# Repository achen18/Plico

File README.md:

# Plico
Fully custom split mechanical keyboard. Runs on ZMK software, controlling key functions and responsive lighting. Future iterations intend to use ultra low-profile switches and a case redesign to allow the two sides to fold together for portability. Firmware updates plan to incorporate layers and macros once the author thinks of what to use so many keys for. 

## PCB
Designed in Kicad

Schematic

PCB

## Case  
3d printed case desinged using Fusion 360. Multiple parts designed for printing with minimal supports. Designed such that no mounting holes needed in pcb. 

## Firmware  
Macropad runs on ZMK software.  
- Split keyboard Bluetooth connection
- 44 keys, full keyboard functionality
- Reactive key leds with fade out effects

To-Do
- Multiple layers for different day-to-day needs. Custom key to easily cycle between layers. Indicate current layer with rgb change. 

## Bill of Materials  
- 2 x XIAO-nRF52840-SMD
- 44 x 1N5819 SMD Diodes
- 44 x MX-Style switches
- 44 x Blank DSA keycaps
- 44 x SK6812-E Reverse Mount LEDs
- 2 x Resistors (1 806k, 1 2M)
- 10 x M3x10 Screws
- 10 x M3x5mx4mm heatset inserts
- 1 x Case (6 3D printed parts - 3 left/right)

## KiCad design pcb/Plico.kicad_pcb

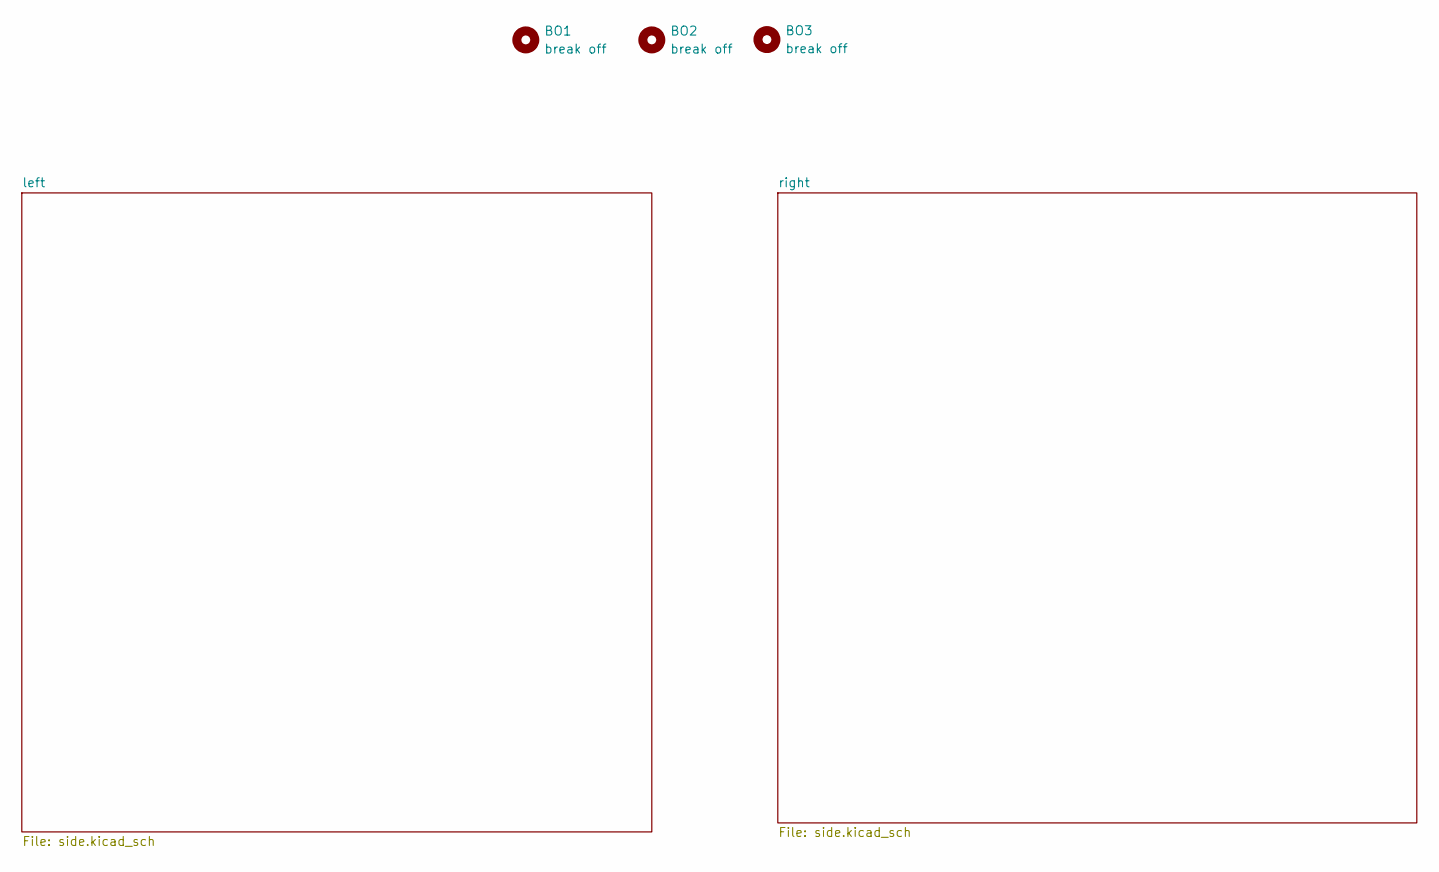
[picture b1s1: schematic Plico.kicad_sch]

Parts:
BO1, BO2, BO3: break off; mouse-bite-5mm-slot-edgeCuts

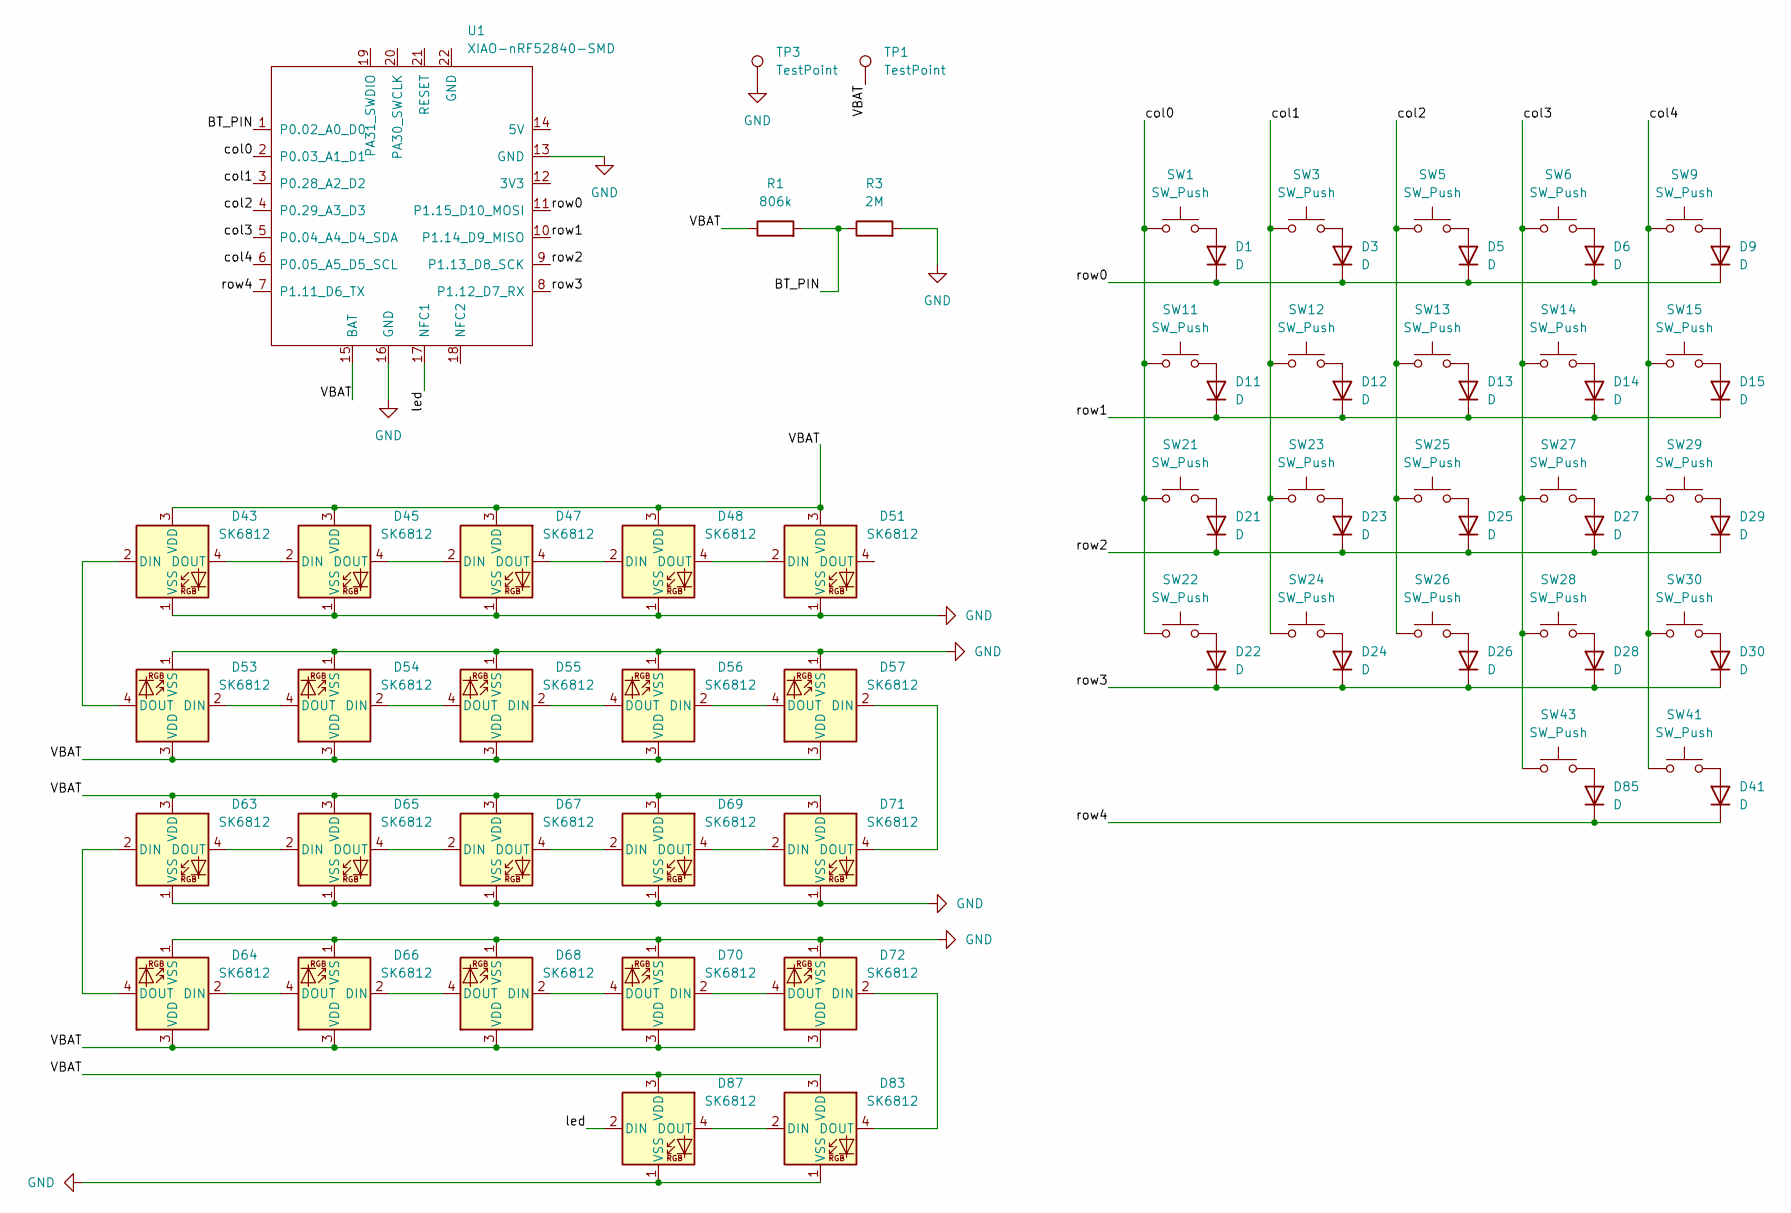
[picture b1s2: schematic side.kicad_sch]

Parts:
D1, D3, D5, D6, D9, D11, D12, D13, D14, D15, D21, D22, D23, D24, D25, D26, D27, D28, D29, D30, D41, D85: D; D_SOD-123
D43, D45, D47, D48, D51, D53, D54, D55, D56, D57, D63, D64, D65, D66, D67, D68, D69, D70, D71, D72, D83, D87: SK6812; Untitled
R1: 806k; R_0805_2012Metric
R3: 2M; R_0805_2012Metric
SW1, SW3, SW5, SW6, SW9, SW11, SW12, SW13, SW14, SW15, SW21, SW22, SW23, SW24, SW25, SW26, SW27, SW28, SW29, SW30, SW41, SW43: SW_Push; SW_MX_HS_CPG151101S11_1u
TP1, TP3: TestPoint; TestPoint_Pad_D2.0mm
U1: XIAO-nRF52840-SMD; modified-XIAO-nRF52840-SMD

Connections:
/left/BT_PIN: R1.2, R3.1, U1.1 (P0.02_A0_D0)
/left/VBAT: D43.3 (VDD), D45.3 (VDD), D47.3 (VDD), D48.3 (VDD), D51.3 (VDD), D53.3 (VDD), D54.3 (VDD), D55.3 (VDD), D56.3 (VDD), D57.3 (VDD), D63.3 (VDD), D64.3 (VDD), D65.3 (VDD), D66.3 (VDD), D67.3 (VDD), D68.3 (VDD), D69.3 (VDD), D70.3 (VDD), D71.3 (VDD), D72.3 (VDD), D83.3 (VDD), D87.3 (VDD), R1.1, TP1.1, U1.15 (BAT)
/left/col0: SW1.1, SW11.1, SW21.1, SW22.1, U1.2 (P0.03_A1_D1)
/left/col1: SW3.1, SW12.1, SW23.1, SW24.1, U1.3 (P0.28_A2_D2)
/left/col2: SW5.1, SW13.1, SW25.1, SW26.1, U1.4 (P0.29_A3_D3)
/left/col3: SW6.1, SW14.1, SW27.1, SW28.1, SW43.1, U1.5 (P0.04_A4_D4_SDA)
/left/col4: SW9.1, SW15.1, SW29.1, SW30.1, SW41.1, U1.6 (P0.05_A5_D5_SCL)
/left/led: D87.2 (DIN), U1.17 (NFC1)
/left/row0: D1.1 (K), D3.1 (K), D5.1 (K), D6.1 (K), D9.1 (K), U1.11 (P1.15_D10_MOSI)
/left/row1: D11.1 (K), D12.1 (K), D13.1 (K), D14.1 (K), D15.1 (K), U1.10 (P1.14_D9_MISO)
/left/row2: D21.1 (K), D23.1 (K), D25.1 (K), D27.1 (K), D29.1 (K), U1.9 (P1.13_D8_SCK)
/left/row3: D22.1 (K), D24.1 (K), D26.1 (K), D28.1 (K), D30.1 (K), U1.8 (P1.12_D7_RX)
/left/row4: D41.1 (K), D85.1 (K), U1.7 (P1.11_D6_TX)
GND: D43.1 (VSS), D45.1 (VSS), D47.1 (VSS), D48.1 (VSS), D51.1 (VSS), D53.1 (VSS), D54.1 (VSS), D55.1 (VSS), D56.1 (VSS), D57.1 (VSS), D63.1 (VSS), D64.1 (VSS), D65.1 (VSS), D66.1 (VSS), D67.1 (VSS), D68.1 (VSS), D69.1 (VSS), D70.1 (VSS), D71.1 (VSS), D72.1 (VSS), D83.1 (VSS), D87.1 (VSS), R3.2, TP3.1, U1.13 (GND), U1.16 (GND); also elsewhere on the board
unnamed: D1.2 (A), SW1.2
unnamed: D3.2 (A), SW3.2
unnamed: D5.2 (A), SW5.2
unnamed: D6.2 (A), SW6.2
unnamed: D9.2 (A), SW9.2
unnamed: D11.2 (A), SW11.2
unnamed: D12.2 (A), SW12.2
unnamed: D13.2 (A), SW13.2
unnamed: D14.2 (A), SW14.2
unnamed: D15.2 (A), SW15.2
unnamed: D21.2 (A), SW21.2
unnamed: D22.2 (A), SW22.2
unnamed: D23.2 (A), SW23.2
unnamed: D24.2 (A), SW24.2
unnamed: D25.2 (A), SW25.2
unnamed: D26.2 (A), SW26.2
unnamed: D27.2 (A), SW27.2
unnamed: D28.2 (A), SW28.2
unnamed: D29.2 (A), SW29.2
unnamed: D30.2 (A), SW30.2
unnamed: D41.2 (A), SW41.2
unnamed: D43.2 (DIN), D53.4 (DOUT)
unnamed: D43.4 (DOUT), D45.2 (DIN)
unnamed: D45.4 (DOUT), D47.2 (DIN)
unnamed: D47.4 (DOUT), D48.2 (DIN)
unnamed: D48.4 (DOUT), D51.2 (DIN)
unnamed: D53.2 (DIN), D54.4 (DOUT)
unnamed: D54.2 (DIN), D55.4 (DOUT)
unnamed: D55.2 (DIN), D56.4 (DOUT)
unnamed: D56.2 (DIN), D57.4 (DOUT)
unnamed: D57.2 (DIN), D71.4 (DOUT)
unnamed: D63.2 (DIN), D64.4 (DOUT)
unnamed: D63.4 (DOUT), D65.2 (DIN)
unnamed: D64.2 (DIN), D66.4 (DOUT)
unnamed: D65.4 (DOUT), D67.2 (DIN)
unnamed: D66.2 (DIN), D68.4 (DOUT)
unnamed: D67.4 (DOUT), D69.2 (DIN)
unnamed: D68.2 (DIN), D70.4 (DOUT)
unnamed: D69.4 (DOUT), D71.2 (DIN)
unnamed: D70.2 (DIN), D72.4 (DOUT)
unnamed: D72.2 (DIN), D83.4 (DOUT)
unnamed: D83.2 (DIN), D87.4 (DOUT)
unnamed: D85.2 (A), SW43.2

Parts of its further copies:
D2, D4, D7, D8, D10, D16, D17, D18, D19, D20, D31, D32, D33, D34, D35, D36, D37, D38, D39, D40, D42, D86: D; D_SOD-123
D44, D46, D49, D50, D52, D58, D59, D60, D61, D62, D73, D74, D75, D76, D77, D78, D79, D80, D81, D82, D84, D88: SK6812; Untitled
R2: 806k; R_0805_2012Metric
R4: 2M; R_0805_2012Metric
SW2, SW4, SW7, SW8, SW10, SW16, SW17, SW18, SW19, SW20, SW31, SW32, SW33, SW34, SW35, SW36, SW37, SW38, SW39, SW40, SW42, SW44: SW_Push; SW_MX_HS_CPG151101S11_1u
TP2, TP4: TestPoint; TestPoint_Pad_D2.0mm
U2: XIAO-nRF52840-SMD; modified-XIAO-nRF52840-SMD

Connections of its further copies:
/right/BT_PIN: R2.2, R4.1, U2.1 (P0.02_A0_D0)
/right/VBAT: D44.3 (VDD), D46.3 (VDD), D49.3 (VDD), D50.3 (VDD), D52.3 (VDD), D58.3 (VDD), D59.3 (VDD), D60.3 (VDD), D61.3 (VDD), D62.3 (VDD), D73.3 (VDD), D74.3 (VDD), D75.3 (VDD), D76.3 (VDD), D77.3 (VDD), D78.3 (VDD), D79.3 (VDD), D80.3 (VDD), D81.3 (VDD), D82.3 (VDD), D84.3 (VDD), D88.3 (VDD), R2.1, TP2.1, U2.15 (BAT)
/right/col0: SW2.1, SW16.1, SW31.1, SW32.1, U2.2 (P0.03_A1_D1)
/right/col1: SW4.1, SW17.1, SW33.1, SW34.1, U2.3 (P0.28_A2_D2)
/right/col2: SW7.1, SW18.1, SW35.1, SW36.1, U2.4 (P0.29_A3_D3)
/right/col3: SW8.1, SW19.1, SW37.1, SW38.1, SW44.1, U2.5 (P0.04_A4_D4_SDA)
/right/col4: SW10.1, SW20.1, SW39.1, SW40.1, SW42.1, U2.6 (P0.05_A5_D5_SCL)
/right/led: D88.2 (DIN), U2.17 (NFC1)
/right/row0: D2.1 (K), D4.1 (K), D7.1 (K), D8.1 (K), D10.1 (K), U2.11 (P1.15_D10_MOSI)
/right/row1: D16.1 (K), D17.1 (K), D18.1 (K), D19.1 (K), D20.1 (K), U2.10 (P1.14_D9_MISO)
/right/row2: D31.1 (K), D33.1 (K), D35.1 (K), D37.1 (K), D39.1 (K), U2.9 (P1.13_D8_SCK)
/right/row3: D32.1 (K), D34.1 (K), D36.1 (K), D38.1 (K), D40.1 (K), U2.8 (P1.12_D7_RX)
/right/row4: D42.1 (K), D86.1 (K), U2.7 (P1.11_D6_TX)
GND: D44.1 (VSS), D46.1 (VSS), D49.1 (VSS), D50.1 (VSS), D52.1 (VSS), D58.1 (VSS), D59.1 (VSS), D60.1 (VSS), D61.1 (VSS), D62.1 (VSS), D73.1 (VSS), D74.1 (VSS), D75.1 (VSS), D76.1 (VSS), D77.1 (VSS), D78.1 (VSS), D79.1 (VSS), D80.1 (VSS), D81.1 (VSS), D82.1 (VSS), D84.1 (VSS), D88.1 (VSS), R4.2, TP4.1, U2.13 (GND), U2.16 (GND); also elsewhere on the board
unnamed: D2.2 (A), SW2.2
unnamed: D4.2 (A), SW4.2
unnamed: D7.2 (A), SW7.2
unnamed: D8.2 (A), SW8.2
unnamed: D10.2 (A), SW10.2
unnamed: D16.2 (A), SW16.2
unnamed: D17.2 (A), SW17.2
unnamed: D18.2 (A), SW18.2
unnamed: D19.2 (A), SW19.2
unnamed: D20.2 (A), SW20.2
unnamed: D31.2 (A), SW31.2
unnamed: D32.2 (A), SW32.2
unnamed: D33.2 (A), SW33.2
unnamed: D34.2 (A), SW34.2
unnamed: D35.2 (A), SW35.2
unnamed: D36.2 (A), SW36.2
unnamed: D37.2 (A), SW37.2
unnamed: D38.2 (A), SW38.2
unnamed: D39.2 (A), SW39.2
unnamed: D40.2 (A), SW40.2
unnamed: D42.2 (A), SW42.2
unnamed: D44.2 (DIN), D58.4 (DOUT)
unnamed: D44.4 (DOUT), D46.2 (DIN)
unnamed: D46.4 (DOUT), D49.2 (DIN)
unnamed: D49.4 (DOUT), D50.2 (DIN)
unnamed: D50.4 (DOUT), D52.2 (DIN)
unnamed: D58.2 (DIN), D59.4 (DOUT)
unnamed: D59.2 (DIN), D60.4 (DOUT)
unnamed: D60.2 (DIN), D61.4 (DOUT)
unnamed: D61.2 (DIN), D62.4 (DOUT)
unnamed: D62.2 (DIN), D81.4 (DOUT)
unnamed: D73.2 (DIN), D74.4 (DOUT)
unnamed: D73.4 (DOUT), D75.2 (DIN)
unnamed: D74.2 (DIN), D76.4 (DOUT)
unnamed: D75.4 (DOUT), D77.2 (DIN)
unnamed: D76.2 (DIN), D78.4 (DOUT)
unnamed: D77.4 (DOUT), D79.2 (DIN)
unnamed: D78.2 (DIN), D80.4 (DOUT)
unnamed: D79.4 (DOUT), D81.2 (DIN)
unnamed: D80.2 (DIN), D82.4 (DOUT)
unnamed: D82.2 (DIN), D84.4 (DOUT)
unnamed: D84.2 (DIN), D88.4 (DOUT)
unnamed: D86.2 (A), SW44.2

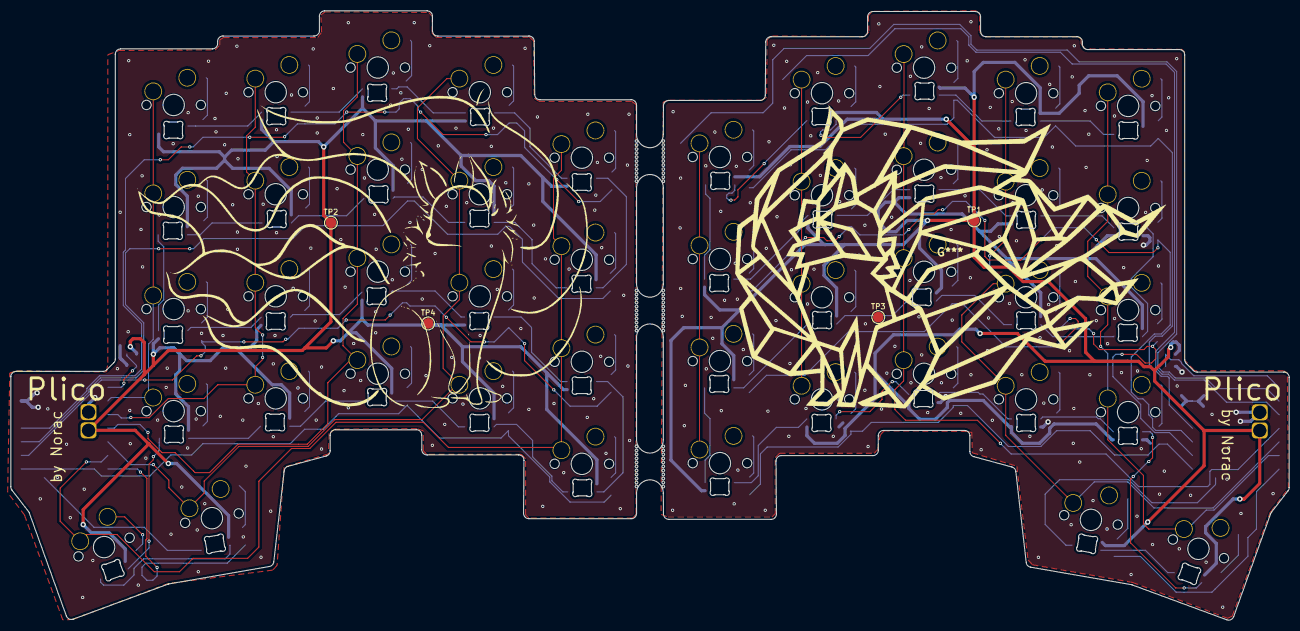
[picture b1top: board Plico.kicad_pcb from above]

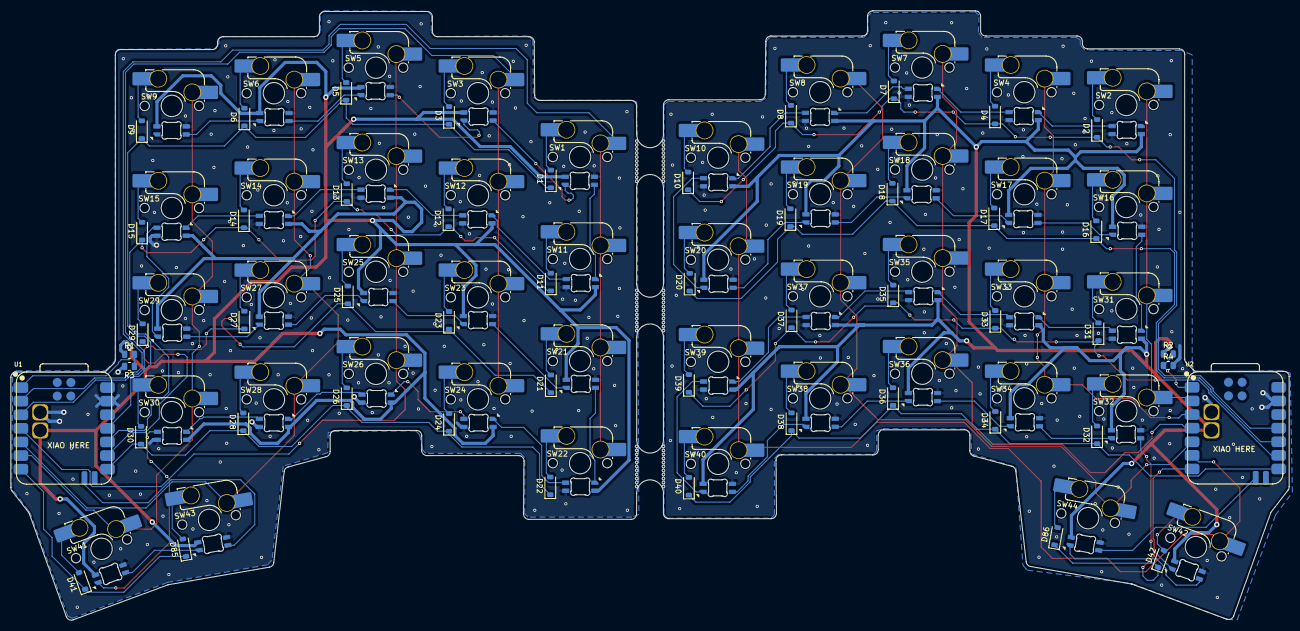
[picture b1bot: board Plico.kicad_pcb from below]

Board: 2 copper layers, 238.6 x 113.7 mm, 145 parts (138 on the bottom side), 113 nets.

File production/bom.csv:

Designator,Footprint,Quantity,Value,LCSC Part #
"D1, D10, D11, D12, D13, D14, D15, D16, D17, D18, D19, D2, D20, D21, D22, D23, D24, D25, D26, D27, D28, D29, D3, D30, D31, D32, D33, D34, D35, D36, D37, D38, D39, D4, D40, D41, D42, D5, D6, D7, D8, D85, D86, D9",D_SOD-123,44,D,
"D43, D44, D45, D46, D47, D48, D49, D50, D51, D52, D53, D54, D55, D56, D57, D58, D59, D60, D61, D62, D63, D64, D65, D66, D67, D68, D69, D70, D71, D72, D73, D74, D75, D76, D77, D78, D79, D80, D81, D82, D83, D84, D87, D88",Untitled,44,SK6812,
"R1, R2",0805,2,806k,
"R3, R4",0805,2,2M,
"SW1, SW10, SW11, SW12, SW13, SW14, SW15, SW16, SW17, SW18, SW19, SW2, SW20, SW21, SW22, SW23, SW24, SW25, SW26, SW27, SW28, SW29, SW3, SW30, SW31, SW32, SW33, SW34, SW35, SW36, SW37, SW38, SW39, SW4, SW40, SW41, SW42, SW43, SW44, SW5, SW6, SW7, SW8, SW9",SW_MX_HS_CPG151101S11_1u,44,SW_Push,
"TP1, TP2, TP3, TP4",TestPoint_Pad_D2.0mm,4,TestPoint,
"U1, U2",modified-XIAO-nRF52840-SMD,2,XIAO-nRF52840-SMD,

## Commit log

2025-12-03 upload
    upload files, no screws in pcb, not started on firmware
2025-12-05 final ?
    am done ?
2026-01-11 Add case left stl's
2026-01-11 Add 3D-print optimized stl's
